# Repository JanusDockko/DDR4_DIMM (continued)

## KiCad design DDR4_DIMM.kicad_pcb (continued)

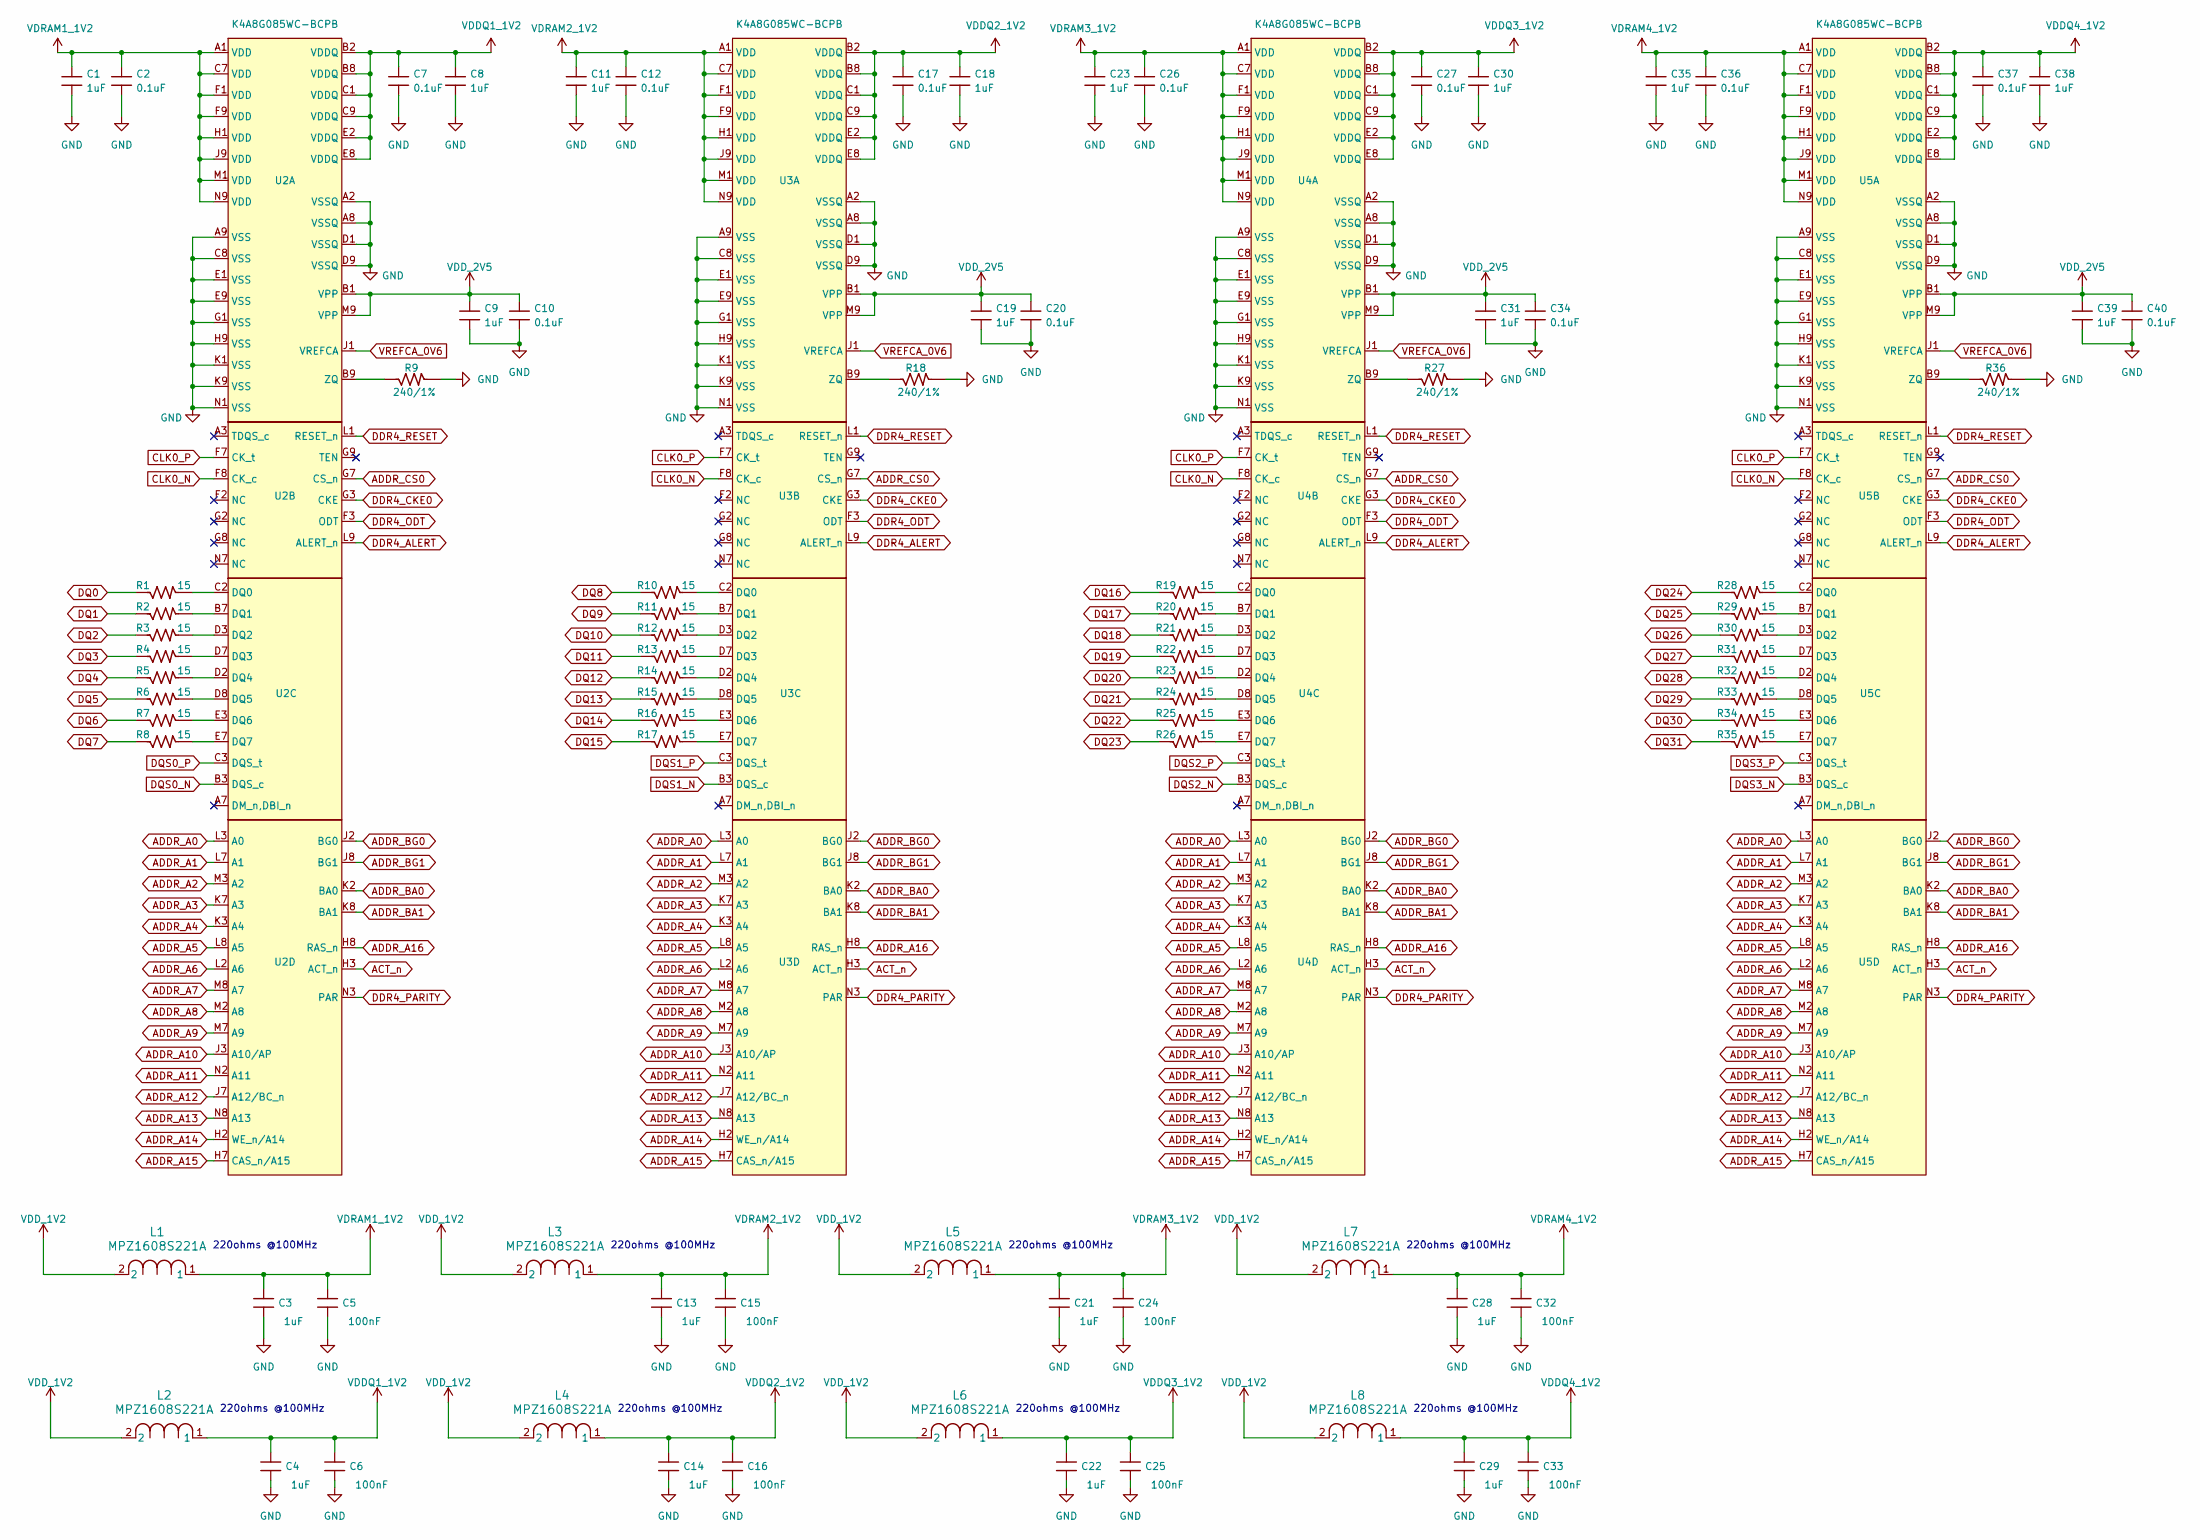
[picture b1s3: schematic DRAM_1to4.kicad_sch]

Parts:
C1, C3, C4, C8, C9, C11, C13, C14, C18, C19, C21, C22, C23, C28, C29, C30, C31, C35, C38, C39: 1uF; C_0402_1005
C2, C7, C10, C12, C17, C20, C26, C27, C34, C36, C37, C40: 0.1uF; C_0402_1005
C5, C6, C15, C16, C24, C25, C32, C33: 100nF; C_0402_1005
L1, L2, L3, L4, L5, L6, L7, L8: MPZ1608S221A; MPZ1608S260ATAH0
R1, R2, R3, R4, R5, R6, R7, R8, R10, R11, R12, R13, R14, R15, R16, R17, R19, R20, R21, R22, R23, R24, R25, R26, R28, R29, R30, R31, R32, R33, R34, R35: 15; R_0402_1005
R9, R18, R27, R36: 240/1%; R_0402_1005
U2, U3, U4, U5: K4A8G085WC-BCPB

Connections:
ACT_n: U2.H3 (ACT_n), U3.H3 (ACT_n), U4.H3 (ACT_n), U5.H3 (ACT_n); also elsewhere on the board
ADDR_A0: U2.L3 (A0), U3.L3 (A0), U4.L3 (A0), U5.L3 (A0); also elsewhere on the board
ADDR_A1: U2.L7 (A1), U3.L7 (A1), U4.L7 (A1), U5.L7 (A1); also elsewhere on the board
ADDR_A2: U2.M3 (A2), U3.M3 (A2), U4.M3 (A2), U5.M3 (A2); also elsewhere on the board
ADDR_A3: U2.K7 (A3), U3.K7 (A3), U4.K7 (A3), U5.K7 (A3); also elsewhere on the board
ADDR_A4: U2.K3 (A4), U3.K3 (A4), U4.K3 (A4), U5.K3 (A4); also elsewhere on the board
ADDR_A5: U2.L8 (A5), U3.L8 (A5), U4.L8 (A5), U5.L8 (A5); also elsewhere on the board
ADDR_A6: U2.L2 (A6), U3.L2 (A6), U4.L2 (A6), U5.L2 (A6); also elsewhere on the board
ADDR_A7: U2.M8 (A7), U3.M8 (A7), U4.M8 (A7), U5.M8 (A7); also elsewhere on the board
ADDR_A8: U2.M2 (A8), U3.M2 (A8), U4.M2 (A8), U5.M2 (A8); also elsewhere on the board
ADDR_A9: U2.M7 (A9), U3.M7 (A9), U4.M7 (A9), U5.M7 (A9); also elsewhere on the board
ADDR_A10: U2.J3 (A10/AP), U3.J3 (A10/AP), U4.J3 (A10/AP), U5.J3 (A10/AP); also elsewhere on the board
ADDR_A11: U2.N2 (A11), U3.N2 (A11), U4.N2 (A11), U5.N2 (A11); also elsewhere on the board
ADDR_A12: U2.J7 (A12/BC_n), U3.J7 (A12/BC_n), U4.J7 (A12/BC_n), U5.J7 (A12/BC_n); also elsewhere on the board
ADDR_A13: U2.N8 (A13), U3.N8 (A13), U4.N8 (A13), U5.N8 (A13); also elsewhere on the board
ADDR_A14: U2.H2 (WE_n/A14), U3.H2 (WE_n/A14), U4.H2 (WE_n/A14), U5.H2 (WE_n/A14); also elsewhere on the board
ADDR_A15: U2.H7 (CAS_n/A15), U3.H7 (CAS_n/A15), U4.H7 (CAS_n/A15), U5.H7 (CAS_n/A15); also elsewhere on the board
ADDR_A16: U2.H8 (RAS_n), U3.H8 (RAS_n), U4.H8 (RAS_n), U5.H8 (RAS_n); also elsewhere on the board
ADDR_BA0: U2.K2 (BA0), U3.K2 (BA0), U4.K2 (BA0), U5.K2 (BA0); also elsewhere on the board
ADDR_BA1: U2.K8 (BA1), U3.K8 (BA1), U4.K8 (BA1), U5.K8 (BA1); also elsewhere on the board
ADDR_BG0: U2.J2 (BG0), U3.J2 (BG0), U4.J2 (BG0), U5.J2 (BG0); also elsewhere on the board
ADDR_BG1: U2.J8 (BG1), U3.J8 (BG1), U4.J8 (BG1), U5.J8 (BG1); also elsewhere on the board
ADDR_CS0: U2.G7 (CS_n), U3.G7 (CS_n), U4.G7 (CS_n), U5.G7 (CS_n); also elsewhere on the board
CLK0_N: U2.F8 (CK_c), U3.F8 (CK_c), U4.F8 (CK_c), U5.F8 (CK_c); also elsewhere on the board
CLK0_P: U2.F7 (CK_t), U3.F7 (CK_t), U4.F7 (CK_t), U5.F7 (CK_t); also elsewhere on the board
DDR4_ALERT: U2.L9 (ALERT_n), U3.L9 (ALERT_n), U4.L9 (ALERT_n), U5.L9 (ALERT_n); also elsewhere on the board
DDR4_CKE0: U2.G3 (CKE), U3.G3 (CKE), U4.G3 (CKE), U5.G3 (CKE); also elsewhere on the board
DDR4_ODT: U2.F3 (ODT), U3.F3 (ODT), U4.F3 (ODT), U5.F3 (ODT); also elsewhere on the board
DDR4_PARITY: U2.N3 (PAR), U3.N3 (PAR), U4.N3 (PAR), U5.N3 (PAR); also elsewhere on the board
DDR4_RESET: U2.L1 (RESET_n), U3.L1 (RESET_n), U4.L1 (RESET_n), U5.L1 (RESET_n); also elsewhere on the board
DQ0: R1.1; also elsewhere on the board
DQ1: R2.1; also elsewhere on the board
DQ2: R3.1; also elsewhere on the board
DQ3: R4.1; also elsewhere on the board
DQ4: R5.1; also elsewhere on the board
DQ5: R6.1; also elsewhere on the board
DQ6: R7.1; also elsewhere on the board
DQ7: R8.1; also elsewhere on the board
DQ8: R10.1; also elsewhere on the board
DQ9: R11.1; also elsewhere on the board
DQ10: R12.1; also elsewhere on the board
DQ11: R13.1; also elsewhere on the board
DQ12: R14.1; also elsewhere on the board
DQ13: R15.1; also elsewhere on the board
DQ14: R16.1; also elsewhere on the board
DQ15: R17.1; also elsewhere on the board
DQ16: R19.1; also elsewhere on the board
DQ17: R20.1; also elsewhere on the board
DQ18: R21.1; also elsewhere on the board
DQ19: R22.1; also elsewhere on the board
DQ20: R23.1; also elsewhere on the board
DQ21: R24.1; also elsewhere on the board
DQ22: R25.1; also elsewhere on the board
DQ23: R26.1; also elsewhere on the board
DQ24: R28.1; also elsewhere on the board
DQ25: R29.1; also elsewhere on the board
DQ26: R30.1; also elsewhere on the board
DQ27: R31.1; also elsewhere on the board
DQ28: R32.1; also elsewhere on the board
DQ29: R33.1; also elsewhere on the board
DQ30: R34.1; also elsewhere on the board
DQ31: R35.1; also elsewhere on the board
DQS0_N: U2.B3 (DQS_c); also elsewhere on the board
DQS0_P: U2.C3 (DQS_t); also elsewhere on the board
DQS1_N: U3.B3 (DQS_c); also elsewhere on the board
DQS1_P: U3.C3 (DQS_t); also elsewhere on the board
DQS2_N: U4.B3 (DQS_c); also elsewhere on the board
DQS2_P: U4.C3 (DQS_t); also elsewhere on the board
DQS3_N: U5.B3 (DQS_c); also elsewhere on the board
DQS3_P: U5.C3 (DQS_t); also elsewhere on the board
GND: C1.1, C2.1, C3.1, C4.1, C5.1, C6.1, C7.1, C8.1, C9.1, C10.1, C11.1, C12.1, C13.1, C14.1, C15.1, C16.1, C17.1, C18.1, C19.1, C20.1, C21.1, C22.1, C23.1, C24.1, C25.1, C26.1, C27.1, C28.1, C29.1, C30.1, C31.1, C32.1, C33.1, C34.1, C35.1, C36.1, C37.1, C38.1, C39.1, C40.1, R9.2, R18.2, R27.2, R36.2, U2.A2 (VSSQ), U2.A8 (VSSQ), U2.A9 (VSS), U2.C8 (VSS), U2.D1 (VSSQ), U2.D9 (VSSQ), U2.E1 (VSS), U2.E9 (VSS), U2.G1 (VSS), U2.H9 (VSS), U2.K1 (VSS), U2.K9 (VSS), U2.N1 (VSS), U3.A2 (VSSQ), U3.A8 (VSSQ), U3.A9 (VSS), U3.C8 (VSS), U3.D1 (VSSQ), U3.D9 (VSSQ), U3.E1 (VSS), U3.E9 (VSS), U3.G1 (VSS), U3.H9 (VSS), U3.K1 (VSS), U3.K9 (VSS), U3.N1 (VSS), U4.A2 (VSSQ), U4.A8 (VSSQ), U4.A9 (VSS), U4.C8 (VSS), U4.D1 (VSSQ), U4.D9 (VSSQ), U4.E1 (VSS), U4.E9 (VSS), U4.G1 (VSS), U4.H9 (VSS), U4.K1 (VSS), U4.K9 (VSS), U4.N1 (VSS), U5.A2 (VSSQ), U5.A8 (VSSQ), U5.A9 (VSS), U5.C8 (VSS), U5.D1 (VSSQ), U5.D9 (VSSQ), U5.E1 (VSS), U5.E9 (VSS), U5.G1 (VSS), U5.H9 (VSS), U5.K1 (VSS), U5.K9 (VSS), U5.N1 (VSS); also elsewhere on the board
unnamed: R9.1, U2.B9 (ZQ)
unnamed: R1.2, U2.C2 (DQ0)
unnamed: R2.2, U2.B7 (DQ1)
unnamed: R3.2, U2.D3 (DQ2)
unnamed: R4.2, U2.D7 (DQ3)
unnamed: R5.2, U2.D2 (DQ4)
unnamed: R6.2, U2.D8 (DQ5)
unnamed: R7.2, U2.E3 (DQ6)
unnamed: R8.2, U2.E7 (DQ7)
unnamed: R18.1, U3.B9 (ZQ)
unnamed: R10.2, U3.C2 (DQ0)
unnamed: R11.2, U3.B7 (DQ1)
unnamed: R12.2, U3.D3 (DQ2)
unnamed: R13.2, U3.D7 (DQ3)
unnamed: R14.2, U3.D2 (DQ4)
unnamed: R15.2, U3.D8 (DQ5)
unnamed: R16.2, U3.E3 (DQ6)
unnamed: R17.2, U3.E7 (DQ7)
unnamed: R27.1, U4.B9 (ZQ)
unnamed: R19.2, U4.C2 (DQ0)
unnamed: R20.2, U4.B7 (DQ1)
unnamed: R21.2, U4.D3 (DQ2)
unnamed: R22.2, U4.D7 (DQ3)
unnamed: R23.2, U4.D2 (DQ4)
unnamed: R24.2, U4.D8 (DQ5)
unnamed: R25.2, U4.E3 (DQ6)
unnamed: R26.2, U4.E7 (DQ7)
unnamed: R36.1, U5.B9 (ZQ)
unnamed: R28.2, U5.C2 (DQ0)
unnamed: R29.2, U5.B7 (DQ1)
unnamed: R30.2, U5.D3 (DQ2)
unnamed: R31.2, U5.D7 (DQ3)
unnamed: R32.2, U5.D2 (DQ4)
unnamed: R33.2, U5.D8 (DQ5)
unnamed: R34.2, U5.E3 (DQ6)
unnamed: R35.2, U5.E7 (DQ7)
VDDQ1_1V2: C4.2, C6.2, C7.2, C8.2, L2.1, U2.B2 (VDDQ), U2.B8 (VDDQ), U2.C1 (VDDQ), U2.C9 (VDDQ), U2.E2 (VDDQ), U2.E8 (VDDQ)
VDDQ2_1V2: C14.2, C16.2, C17.2, C18.2, L4.1, U3.B2 (VDDQ), U3.B8 (VDDQ), U3.C1 (VDDQ), U3.C9 (VDDQ), U3.E2 (VDDQ), U3.E8 (VDDQ)
VDDQ3_1V2: C22.2, C25.2, C27.2, C30.2, L6.1, U4.B2 (VDDQ), U4.B8 (VDDQ), U4.C1 (VDDQ), U4.C9 (VDDQ), U4.E2 (VDDQ), U4.E8 (VDDQ)
VDDQ4_1V2: C29.2, C33.2, C37.2, C38.2, L8.1, U5.B2 (VDDQ), U5.B8 (VDDQ), U5.C1 (VDDQ), U5.C9 (VDDQ), U5.E2 (VDDQ), U5.E8 (VDDQ)
VDD_1V2: L1.2, L2.2, L3.2, L4.2, L5.2, L6.2, L7.2, L8.2; also elsewhere on the board
VDD_2V5: C9.2, C10.2, C19.2, C20.2, C31.2, C34.2, C39.2, C40.2, U2.B1 (VPP), U2.M9 (VPP), U3.B1 (VPP), U3.M9 (VPP), U4.B1 (VPP), U4.M9 (VPP), U5.B1 (VPP), U5.M9 (VPP); also elsewhere on the board
VDRAM1_1V2: C1.2, C2.2, C3.2, C5.2, L1.1, U2.A1 (VDD), U2.C7 (VDD), U2.F1 (VDD), U2.F9 (VDD), U2.H1 (VDD), U2.J9 (VDD), U2.M1 (VDD), U2.N9 (VDD)
VDRAM2_1V2: C11.2, C12.2, C13.2, C15.2, L3.1, U3.A1 (VDD), U3.C7 (VDD), U3.F1 (VDD), U3.F9 (VDD), U3.H1 (VDD), U3.J9 (VDD), U3.M1 (VDD), U3.N9 (VDD)
VDRAM3_1V2: C21.2, C23.2, C24.2, C26.2, L5.1, U4.A1 (VDD), U4.C7 (VDD), U4.F1 (VDD), U4.F9 (VDD), U4.H1 (VDD), U4.J9 (VDD), U4.M1 (VDD), U4.N9 (VDD)
VDRAM4_1V2: C28.2, C32.2, C35.2, C36.2, L7.1, U5.A1 (VDD), U5.C7 (VDD), U5.F1 (VDD), U5.F9 (VDD), U5.H1 (VDD), U5.J9 (VDD), U5.M1 (VDD), U5.N9 (VDD)
VREFCA_0V6: U2.J1 (VREFCA), U3.J1 (VREFCA), U4.J1 (VREFCA), U5.J1 (VREFCA); also elsewhere on the board

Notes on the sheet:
220ohms @100MHz

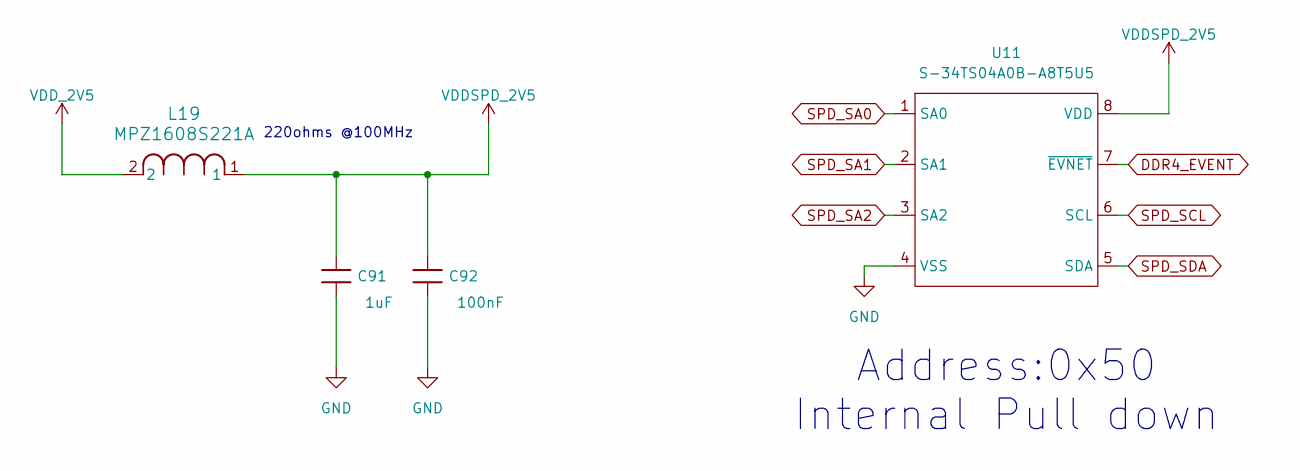
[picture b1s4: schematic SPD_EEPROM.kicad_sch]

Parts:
C91: 1uF; R_0402_1005
C92: 100nF; R_0402_1005
L19: MPZ1608S221A; MPZ1608S260ATAH0
U11: S-34TS04A0B-A8T5U5

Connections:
DDR4_EVENT: U11.7 (~EVNET); also elsewhere on the board
GND: C91.1, C92.1, U11.4 (VSS); also elsewhere on the board
SPD_SA0: U11.1 (SA0); also elsewhere on the board
SPD_SA1: U11.2 (SA1); also elsewhere on the board
SPD_SA2: U11.3 (SA2); also elsewhere on the board
SPD_SCL: U11.6 (SCL); also elsewhere on the board
SPD_SDA: U11.5 (SDA); also elsewhere on the board
VDDSPD_2V5: C91.2, C92.2, L19.1, U11.8 (VDD); also elsewhere on the board
VDD_2V5: L19.2; also elsewhere on the board

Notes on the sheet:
220ohms @100MHz
Address:0x50 Internal Pull down

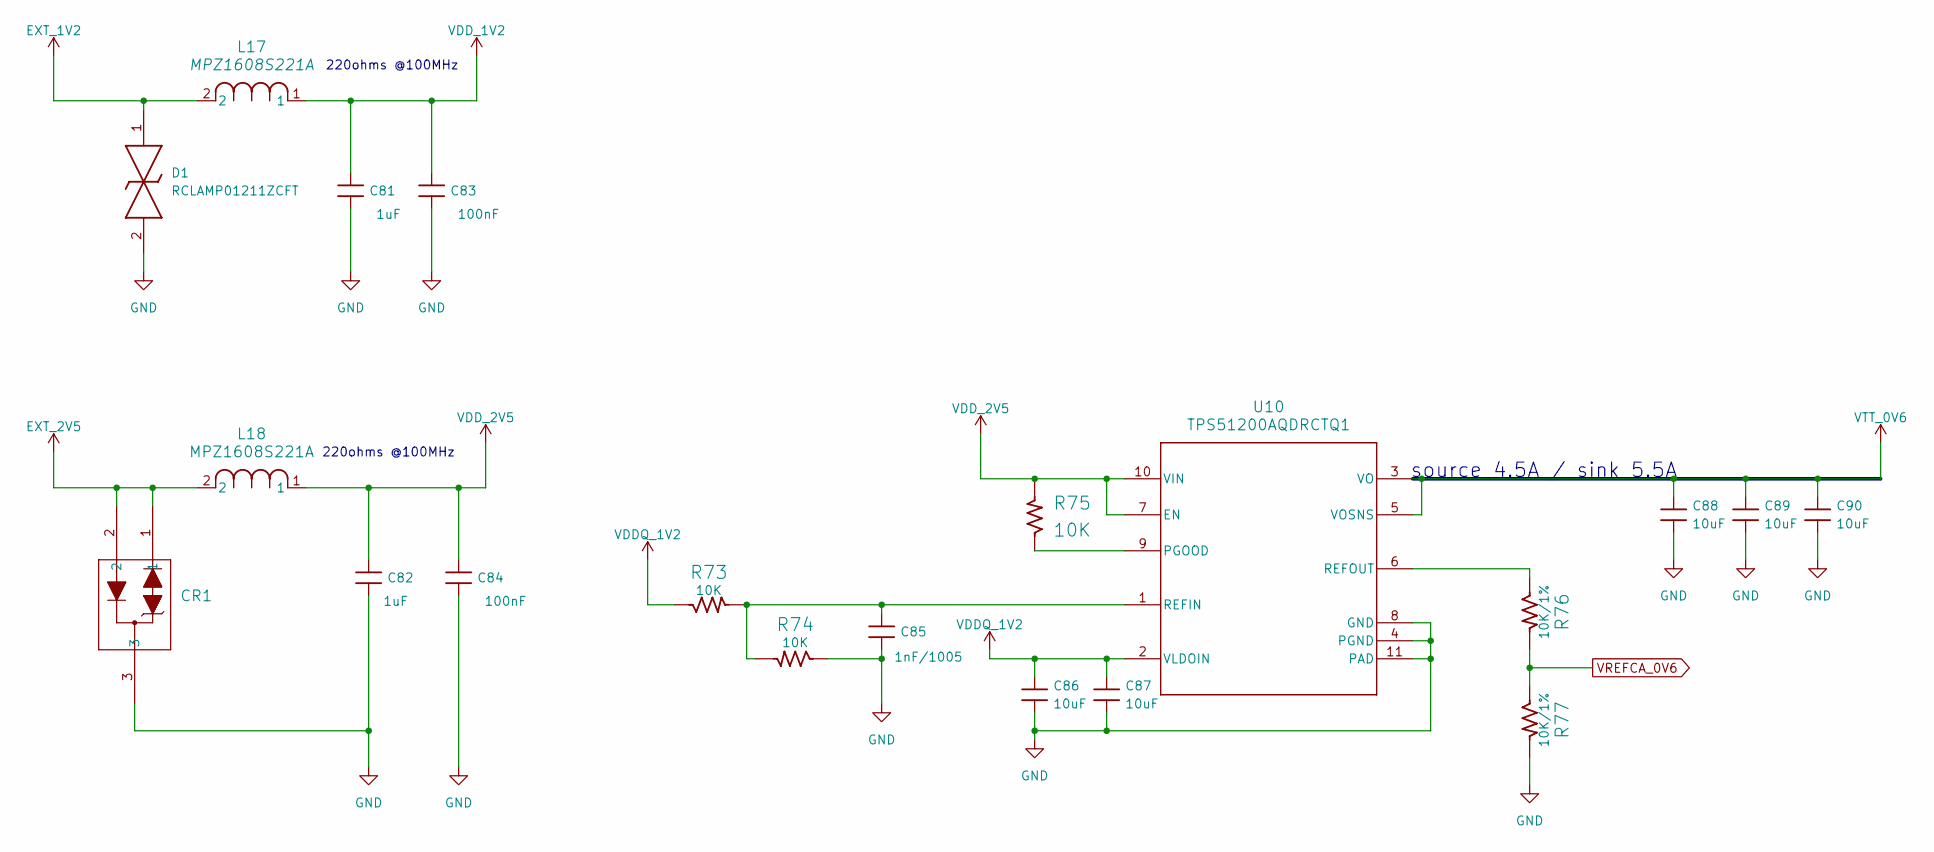
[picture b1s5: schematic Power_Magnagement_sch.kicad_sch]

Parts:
C81, C82: 1uF; C_0402_1005
C83, C84: 100nF; C_0402_1005
C85: 1nF/1005; C_0402_1005
C86, C87, C88, C89, C90: 10uF; C_0603_1608
CR1: SLVU2.8HTG
D1: RCLAMP01211ZCFT; Manufacturer_Part_Number RCLAMP01211ZCFT; Mouser Part Number 947-RCLAMP01211ZCFT
L17, L18: MPZ1608S221A; MPZ1608S260ATAH0
R73, R74, R75: 10K; R_0402_1005; Manufacturer Part Number WR06X1002FTL
R76, R77: 10K/1%; R_0603_1608; Manufacturer Part Number WR06X1002FTL
U10: TPS51200AQDRCTQ1; DRC0010J

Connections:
EXT_1V2: D1.1, L17.2; also elsewhere on the board
EXT_2V5: CR1.1, CR1.2, L18.2; also elsewhere on the board
GND: C81.1, C82.1, C83.1, C84.1, C85.1, C86.1, C87.1, C88.1, C89.1, C90.1, CR1.3, D1.2, R74.1, R77.2, U10.4 (PGND), U10.8 (GND), U10.11 (PAD); also elsewhere on the board
unnamed: R75.1, U10.9 (PGOOD)
unnamed: C85.2, R73.2, R74.2, U10.1 (REFIN)
unnamed: R76.1, U10.6 (REFOUT)
VDDQ_1V2: C86.2, C87.2, R73.1, U10.2 (VLDOIN)
VDD_1V2: C81.2, C83.2, L17.1; also elsewhere on the board
VDD_2V5: C82.2, C84.2, L18.1, R75.2, U10.7 (EN), U10.10 (VIN); also elsewhere on the board
VREFCA_0V6: R76.2, R77.1; also elsewhere on the board
VTT_0V6: C88.2, C89.2, C90.2, U10.3 (VO), U10.5 (VOSNS); also elsewhere on the board

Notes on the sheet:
220ohms @100MHz
source 4.5A / sink 5.5A

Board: 6 copper layers, 201 parts (0 on the bottom side), 216 nets, no tracks yet.

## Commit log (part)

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2025-07-21 Making DDR4 DRAM footprint
2025-07-21 Making DDR4 DRAM Symbol and footprint
2025-07-27 Adding DIMM Connector Footprint, Symbol and Pin Desciption.
2026-06-21 Modifying DIMM Edge connector Footprint
2026-06-28 Adding Edge connector schematic
